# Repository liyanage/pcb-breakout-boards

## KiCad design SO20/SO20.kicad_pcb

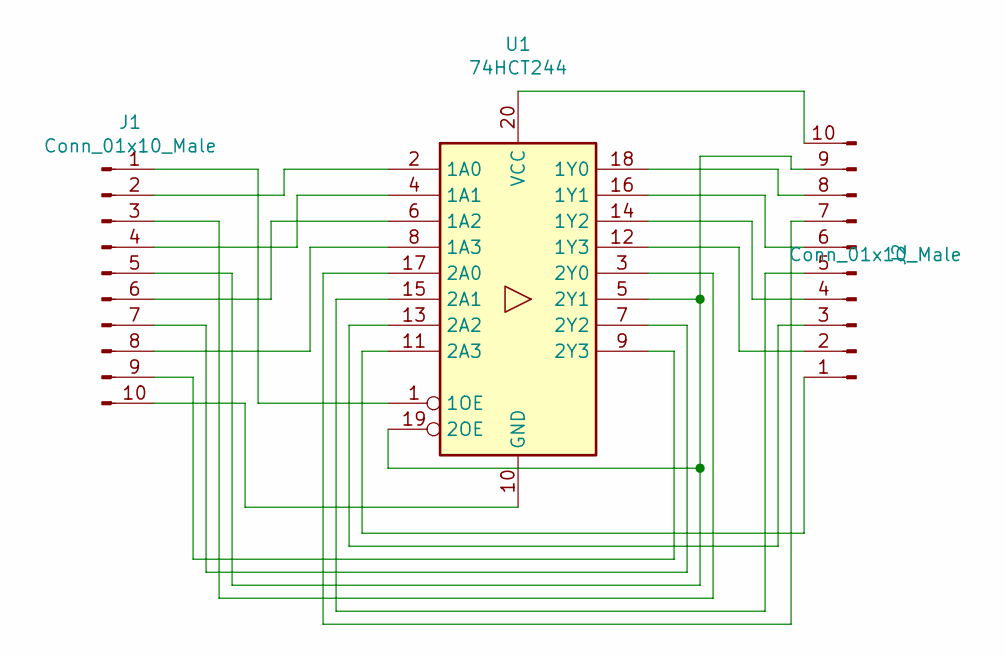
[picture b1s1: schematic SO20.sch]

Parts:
J1, J2: Conn_01x10_Male; PinHeader_1x10_P2.54mm_Vertical
U1: 74HCT244; SO-20_12.8x7.5mm_P1.27mm

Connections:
unnamed: J1.1, U1.1 (1OE)
unnamed: J1.2, U1.2 (1A0)
unnamed: J1.3, U1.3 (2Y0)
unnamed: J1.4, U1.4 (1A1)
unnamed: J1.5, J2.9, U1.5 (2Y1), U1.19 (2OE)
unnamed: J1.6, U1.6 (1A2)
unnamed: J1.7, U1.7 (2Y2)
unnamed: J1.8, U1.8 (1A3)
unnamed: J1.9, U1.9 (2Y3)
unnamed: J1.10, U1.10 (GND)
unnamed: J2.1, U1.11 (2A3)
unnamed: J2.2, U1.12 (1Y3)
unnamed: J2.3, U1.13 (2A2)
unnamed: J2.4, U1.14 (1Y2)
unnamed: J2.5, U1.15 (2A1)
unnamed: J2.6, U1.16 (1Y1)
unnamed: J2.7, U1.17 (2A0)
unnamed: J2.8, U1.18 (1Y0)
unnamed: J2.10, U1.20 (VCC)

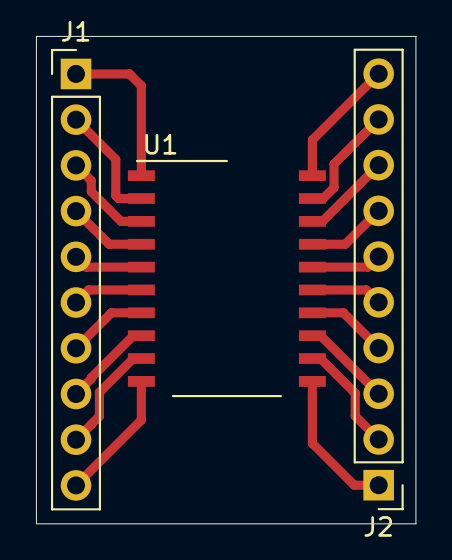
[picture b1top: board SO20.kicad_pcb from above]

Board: 2 copper layers, 21.1 x 27.1 mm, 3 parts (0 on the bottom side), 19 nets.

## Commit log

2019-12-05 init
